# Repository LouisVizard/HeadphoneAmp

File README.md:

# 🎸 Guitar Headphone Amplifier

**A compact, single-supply headphone amplifier for electric guitar, built around a paralleled NE5532 output stage**

---

## 📌 Overview

The **Guitar Headphone Amplifier** is a custom PCB designed to drive low-impedance headphones directly from an electric guitar signal — no computer audio interface required. The board operates from a single 9V supply using a virtual ground at VCC/2, and features a paralleled op-amp output stage capable of cleanly driving 32Ω loads without a discrete transistor buffer stage.

> Hardware design is complete. The board was designed, simulated, and laid out in full at Cornell University in 2022.

---

## ⚡ Specifications

| Parameter | Value |
|---|---|
| **Op-Amp** | NE5532 (×4, paralleled output stage) |
| **Power Supply** | 9V DC via barrel jack |
| **Input** | Electric guitar, mono |
| **Output** | 3.5mm headphone jack |
| **Volume Control** | 100kΩ potentiometer |
| **PCB Stackup** | 2-layer, KiCAD |

---

## 🏗️ Signal Chain

```
┌──────────────┐     ┌──────────────────┐     ┌──────────────────────────┐     ┌──────────────┐     ┌──────────────┐
│              │     │                  │     │                          │     │              │     │              │
│  Guitar In   │────▶│  Input Buffer    │────▶│  ×4 Parallel Output      │────▶│  Volume Pot  │────▶│  Headphone   │
│  (J3)        │     │  U1A — NE5532    │     │  Stage  U2–U3 — NE5532   │     │  RV1 100kΩ   │     │  Out (J1)    │
│              │     ├──────────────────┤     │                          │     │              │     │              │
│              │     │  Active Filter   │     │                          │     │              │     │              │
│              │     │  U1B — NE5532    │     │                          │     │              │     │              │
└──────────────┘     └──────────────────┘     └──────────────────────────┘     └──────────────┘     └──────────────┘
```

A virtual ground at VCC/2 enables single-supply operation. Coupling capacitors block DC from the headphone output.

---

## 🔧 Design Details

### Op-Amp Selection — NE5532 over LM358

The initial design used an **LM358**. Transient simulation in LTSpice exposed a critical flaw: crossover distortion appearing at frequencies as low as 5–10 kHz. This notching artifact near the zero-crossing is clearly audible and disqualifies the LM358 from audio signal paths.

The pin-compatible **NE5532** was substituted and resolved the issue entirely:

- Industry-standard audio op-amp with input voltage noise of **5 nV/√Hz**
- Significantly higher slew rate than the LM358
- Simulation confirmed clean, undistorted output across the full **20 Hz – 20 kHz** audio band

### Paralleled Output Stage

Driving 32Ω headphones requires more output current than a single op-amp section can supply without distortion. Rather than adding a discrete BJT output stage, **four NE5532 sections are wired in parallel**:

- Multiplies available output current by **4×**
- Averages individual op-amp noise contributions
- Eliminates bias complexity associated with class-AB transistor stages

### PCB Layout

The 2-layer board was laid out in KiCAD with the following considerations:

- Copper pour ground plane on the bottom layer for noise rejection
- Decoupling capacitors placed directly at each op-amp supply pin
- Ferrite bead (FB1) and protection diode (D2) at the audio output
- All panel connectors (barrel jack, potentiometer, audio jacks) placed at board edges for clean enclosure mounting

---

## 🗺️ Roadmap

- [x] Schematic capture and component selection
- [x] LTSpice simulation — LM358 vs NE5532 comparison
- [x] PCB layout and design rule check
- [ ] Bench measurement of THD+N and SNR; comparison against simulation
- [ ] Baxandall tone control in place of simple volume potentiometer
- [ ] Laser-cut or 3D-printed enclosure

---

## 🛠️ Tech Stack

| Layer | Technology |
|---|---|
| **Schematic & PCB** | KiCAD |
| **Simulation** | LTSpice |
| **Core Component** | NE5532 audio op-amp |

---

## 👤 Author

**Luis Martinez**

---

*Built with KiCAD · LTSpice · NE5532*

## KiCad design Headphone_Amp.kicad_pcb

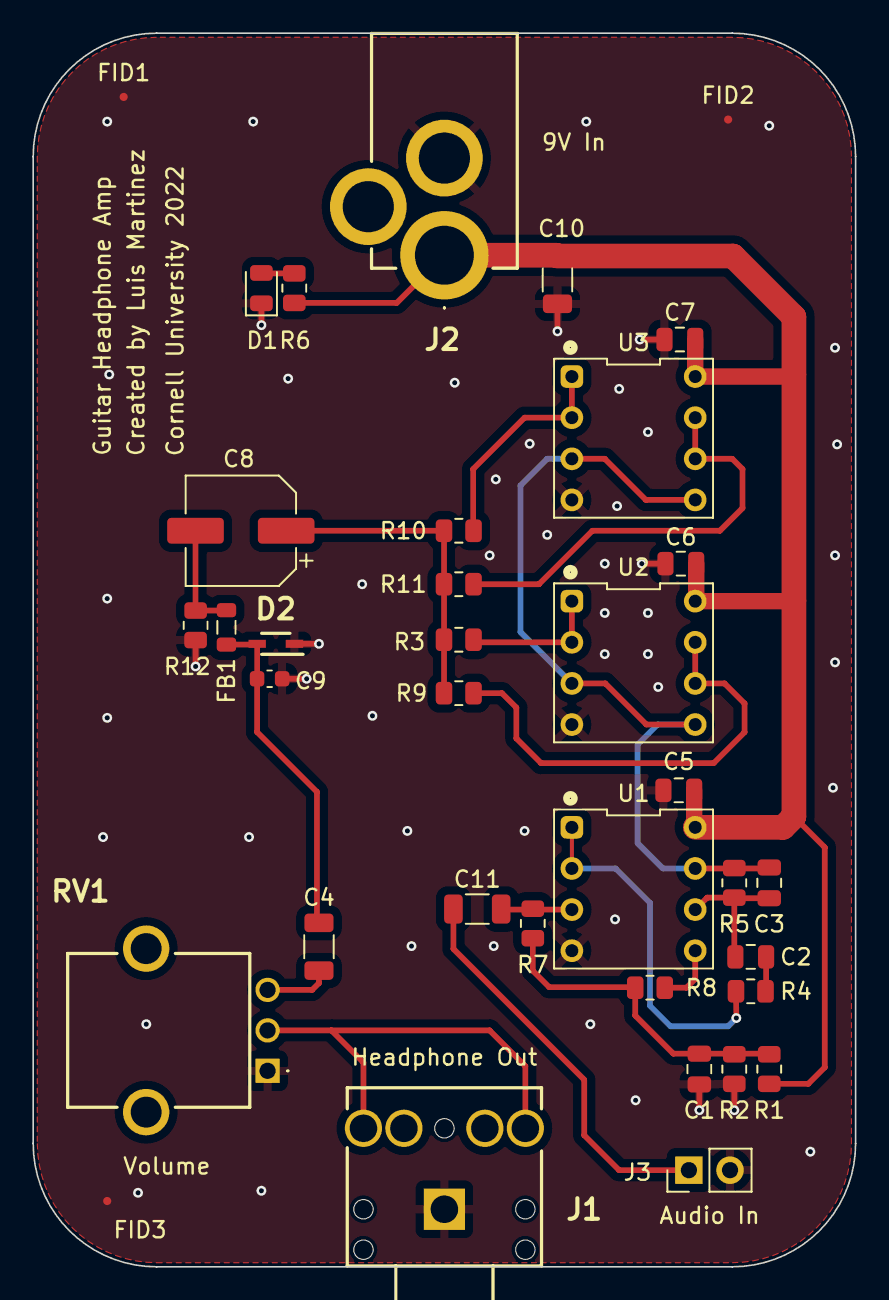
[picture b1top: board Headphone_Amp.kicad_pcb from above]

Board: 2 copper layers, 50.8 x 76.2 mm, 36 parts (0 on the bottom side), 20 nets.

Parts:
C1: 4.7uF; C_0805_2012Metric
C2: 390nF; C_0805_2012Metric
C3: 51pF; C_0805_2012Metric
C4, C11: 10uF; C_1206_3216Metric
C5, C6, C7: 0.1uF; C_0805_2012Metric
C8: 100uF; CP_Elec_6.3x5.9
C9: 30pF; C_0603_1608Metric
C10: 22uF; C_1206_3216Metric
D1: APT2012LSECK/J3-PRV; D_0805_2012Metric
D2: CDSOD323-T03SC
FB1: 120R; L_0805_2012Metric
FID1, FID2, FID3: Fiducial; Fiducial_0.5mm_Mask1mm
J1: PRT-08032; PRT08032
J2: PRT-00119; PRT00119
J3: Conn_01x02; PinHeader_1x02_P2.54mm_Vertical
R1, R2, R4: 10k; R_0805_2012Metric
R3, R9, R10, R11: 1; R_0805_2012Metric
R5: 100k; R_0805_2012Metric
R6: 3.6k; R_0805_2012Metric
R7, R8: 470k; R_0805_2012Metric
R12: 1.8k; R_0805_2012Metric
RV1: 100k; PTN091V100115K1B
U1, U2, U3: NE5532; NE5532_8DIP

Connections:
AUDIO_FILT: C3.2, R5.2, U1.7, U2.3 (+), U2.5 (+), U3.3 (+), U3.5 (+)
AUDIO_OUT: C4.1, C9.1, D2.2 (A2), FB1.2
GND: C1.2, C5.1, C6.1, C7.1, C9.2, C10.2, D1.1 (K), D2.1 (A1), J1.G, J2.2, J3.2, R2.2, R12.2, RV1.1, U1.4 (V-), U2.4 (V-), U3.4 (V-)
unnamed: C2.1, R4.2
unnamed: C4.2, RV1.3
unnamed: C8.1, R3.2, R9.2, R10.2, R11.2
unnamed: C8.2, FB1.1, R12.1
unnamed: D1.2 (A), R6.2
unnamed: J1.S, J1.T, RV1.2
unnamed: C11.2, R7.2, U1.3 (+)
unnamed: R4.1, U1.1, U1.2 (-)
unnamed: R8.2, U1.5 (+)
unnamed: C2.2, C3.1, R5.1, U1.6 (-)
unnamed: R3.1, U2.1, U2.2 (-)
unnamed: R9.1, U2.6 (-), U2.7
unnamed: R10.1, U3.1, U3.2 (-)
unnamed: R11.1, U3.6 (-), U3.7
SIG_IN: C11.1, J3.1
VBias: C1.1, R1.2, R2.1, R7.1, R8.1
VCC: C5.2, C6.2, C7.2, C10.1, J2.1, R1.1, R6.1, U1.8 (V+), U2.8 (V+), U3.8 (V+)
